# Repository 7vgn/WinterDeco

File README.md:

# Winter Decoration

Every year since 2023, I have created a winter-themed piece of decoration based on a custom-made PCB. The primary goal was to get some SMD soldering practice, but they also make nice presents. 

* [Evergreen Tree](2023/) (2023)
* [Simon the Snowman](2024/) (2024)
* [Old-fashioned Computer](2025/) (2025)
* [Spider Web](2026/) (2026)

All projects run on a CR2032 coin cell and feature the [PIC18F14Q41](https://www.microchip.com/en-us/product/pic18f14q41) microcontroller. The firmware was developed in [MPLAB X](https://www.microchip.com/en-us/tools-resources/develop/mplab-x-ide) using the [XC8](https://www.microchip.com/en-us/tools-resources/develop/mplab-xc-compilers/xc8) compiler. You need a PIC programmer such as PICkit, SNAP, or a suitable third-party clone to flash the firmware. 

The PCBs were designed with [KiCAD](https://www.kicad.org/). Ready-to-manufacture Gerber files for JLCPCB are included.

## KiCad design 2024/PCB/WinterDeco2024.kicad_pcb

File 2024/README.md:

# Winter Decoration 2024

The 2024 winter-themed decoration is Simon the Snowman. Simon has five touch-sensitive buttons. A long press of the lower right button turns him on of off. When turned on, a short press on each of the five buttons switches to a unique program. Simon also has a hidden secret game. Can you find it without looking at the code?

The touch sensors are implemented using the [PIC18F14Q41](https://www.microchip.com/en-us/product/pic18f14q41)'s capacitive voltage divider (CVD) feature. You can learn more about CVD in Microchip's Application Notes [1478](https://ww1.microchip.com/downloads/en/appnotes/01478A.pdf) and [2934](https://ww1.microchip.com/downloads/en/AppNotes/AN2934-Capacitive-Touch-Sensor-Design-Guidelines-00002934A.pdf). 

## Bill of Materials

| Ref | Qty | Part | Value | Links[^links]
| --- | ---:| --- | --- | --- |
| - | 1 | PCB | 2-layer, 1.6mm thickness, white soldermask, black silkscreen, ENIG[^enig] | [J](https://jlcpcb.com/)
| BT1 | 1 | Battery Clip | CR2032, SMD mount | [M](https://mouser.com/ProductDetail/?qs=sGAEpiMZZMvxqoKe%252BDjhrhkd9JgmX6KPIe2Fc6FHFcOAlHTLYwGDJA%3D%3D) [D](https://www.digikey.com/en/products/detail/te-connectivity-linx/BAT-HLD-003-SMT-TR/14301788?s=N4IgTCBcDaIEIEEAqBaAEgGQCIoAy4GYUBlAWVSQCUQBdAXyA) [R](https://www.reichelt.de/shop/produkt/knopfzellenclip_fuer_20_mm_smd-56574)
| C1 | 1 | Capacitor | SMD 1206, 100µF, X5R | [M](https://mouser.com/ProductDetail/?qs=pUKx8fyJudDzdyEEakAKPA%3D%3D) [D](https://www.digikey.com/en/products/detail/murata-electronics/GRM31CR60J107KEA8L/16286000?s=N4IgTCBcDaIOICUCyBmAjAYQQNgAwCk1cB2AaQFEBBADgBkQBdAXyA) [R](https://www.reichelt.de/shop/produkt/mlcc_1206_100_f_6_3_v_-10_x5r-409219)
| D* | 12 | LED | SMD 1206, yellow | [M](https://mouser.com/ProductDetail/?qs=sGAEpiMZZMv0DJfhVcWlK%252BdbpgZMtcHOeXAaxJ3bARo%3D) [D](https://www.digikey.com/en/products/detail/liteon/LTST-C150YKT/269217?s=N4IgTCBcDaIDIBUDKCC0BhAjAVgAwE0BpBEAXQF8g) [R](https://www.reichelt.de/shop/produkt/led_smd_1206_gelb_150_mcd_120_-361548)
| D* | 6 | LED | SMD 1206, red (mouth) | [M](https://mouser.com/ProductDetail/?qs=sGAEpiMZZMv0DJfhVcWlK%252BdbpgZMtcHOPtGkXd2H%2F2o%3D) [D](https://www.digikey.com/en/products/detail/liteon/LTST-C150KRKT/386761?s=N4IgTCBcDaIDIBUDKCC0BhAjAVgAwGkAlfBEAXQF8g) [R](https://www.reichelt.de/de/de/shop/produkt/led_smd_1206_rot_150_mcd_120_-361547)
| D* | 5 | LED | SMD 1206, green (buttons) | [M](https://mouser.com/ProductDetail/?qs=sGAEpiMZZMv0DJfhVcWlK%252BdbpgZMtcHOivY63VReAjk%3D) [D](https://www.digikey.com/en/products/detail/liteon/LTST-C150KGKT/365085?s=N4IgTCBcDaIDIBUDKCC0BhAjAVgAwGkBxfBEAXQF8g) [R](https://www.reichelt.de/de/de/shop/produkt/led_smd_1206_gruen_500_mcd_120_-361549)
| D* | 1 | LED | SMD 1206, orange (nose) | [M](https://mouser.com/ProductDetail/?qs=sGAEpiMZZMv0DJfhVcWlK%252BdbpgZMtcHO1szBFqLoZwU%3D) [D](https://www.digikey.com/en/products/detail/liteon/LTST-C150KFKT/386758?s=N4IgTCBcDaIDIBUDKCC0BhAjAVgAwGkAxfBEAXQF8g) [R](https://www.reichelt.de/de/de/shop/produkt/smd-led_superhell_orange_200_mcd_120_3_2_x_1_6_mm_1206_-231710)
| Q1[^polprot] | 1 | P-MOSFET | IRLML6402, SOT-23 | [M](https://mouser.com/ProductDetail/?qs=9%252BKlkBgLFf0HuZuONx2Ewg%3D%3D) [D](https://www.digikey.com/en/products/detail/infineon-technologies/IRLML6402TRPBF/811437) [R](https://www.reichelt.de/shop/produkt/mosfet_p-ch_-20v_-3_7a_0_065r_sot-23-108743)
| R1..4 | 4 | Resistor | SMD 1206, 68Ω | [M](https://mouser.com/ProductDetail/?qs=CteSnpDdeuDJTICysoGhNw%3D%3D) [D](https://www.digikey.com/en/products/detail/yageo/RC1206JR-0768RL/729330?s=N4IgTCBcDaIEoGECMYAMA2AUnAtKg7OgBxwAyIAugL5A) [R](https://www.reichelt.de/shop/produkt/smd-widerstand_1206_68_ohm_250_mw_5_-18364)
| R5 | 1 | Resistor | SMD 1206, 3.3kΩ | [M](https://mouser.com/ProductDetail/?qs=CteSnpDdeuDJAlQtfVL%252BIw%3D%3D) [D](https://www.digikey.com/en/products/detail/yageo/RC1206JR-073K3L/729267?s=N4IgTCBcDaIEoGECMYAMA2AUnAtKg7AMwDShAMiALoC%2BQA) [R](https://www.reichelt.de/shop/produkt/smd-widerstand_1206_3_3_kohm_250_mw_5_-18302)
| R6 | 1 | Resistor | SMD 1206, 4.7kΩ | [M](https://mouser.com/ProductDetail/?qs=CteSnpDdeuDgOu3Rsm1uRA%3D%3D) [D](https://www.digikey.com/en/products/detail/yageo/RC1206JR-074K7L/729295?s=N4IgTCBcDaIEoGECMYAMA2AUnAtKg7ACwDS%2BAMiALoC%2BQA) [R](https://www.reichelt.de/shop/produkt/smd-widerstand_1206_4_7_kohm_250_mw_5_-18330)
| U1 | 1 | Microcontroller | PIC18F14Q41-I/SO, SOIC-14 | [M](https://mouser.com/ProductDetail/?qs=W%2FMpXkg%252BdQ5jNCMT7LkJWg%3D%3D) [D](https://www.digikey.com/en/products/detail/microchip-technology/PIC18F14Q41-I-SO/13415037?s=N4IgTCBcDaIA4EsDGBGAHAMxQFgI7ZQFoEB6AZwHsQBdAXyA) [R](https://www.reichelt.de/shop/produkt/8-bit-picmicro_mikrocontroller_16_kb_64_mhz_so-20-311092)
| - | 1 | Piece of String | |
| - | 1 | Coin Cell | CR2032 |

[^links]: Links are just examples. Other sellers are available and similar parts can be substituted.  
[^enig]: ENIG is not required, but at JLCPCB the combination of white soldermask and lead-free HASL comes with a surcharge which makes ENIG the cheaper option.  
[^polprot]: Q1 protects against reverse polarity and is optional. If left out, the solder jumper JP1 must be bridged instead. 

Required tools and materials: soldering iron, lead-free solder, tweezers, flux, isopropyl alcohol for cleaning, PIC programmer

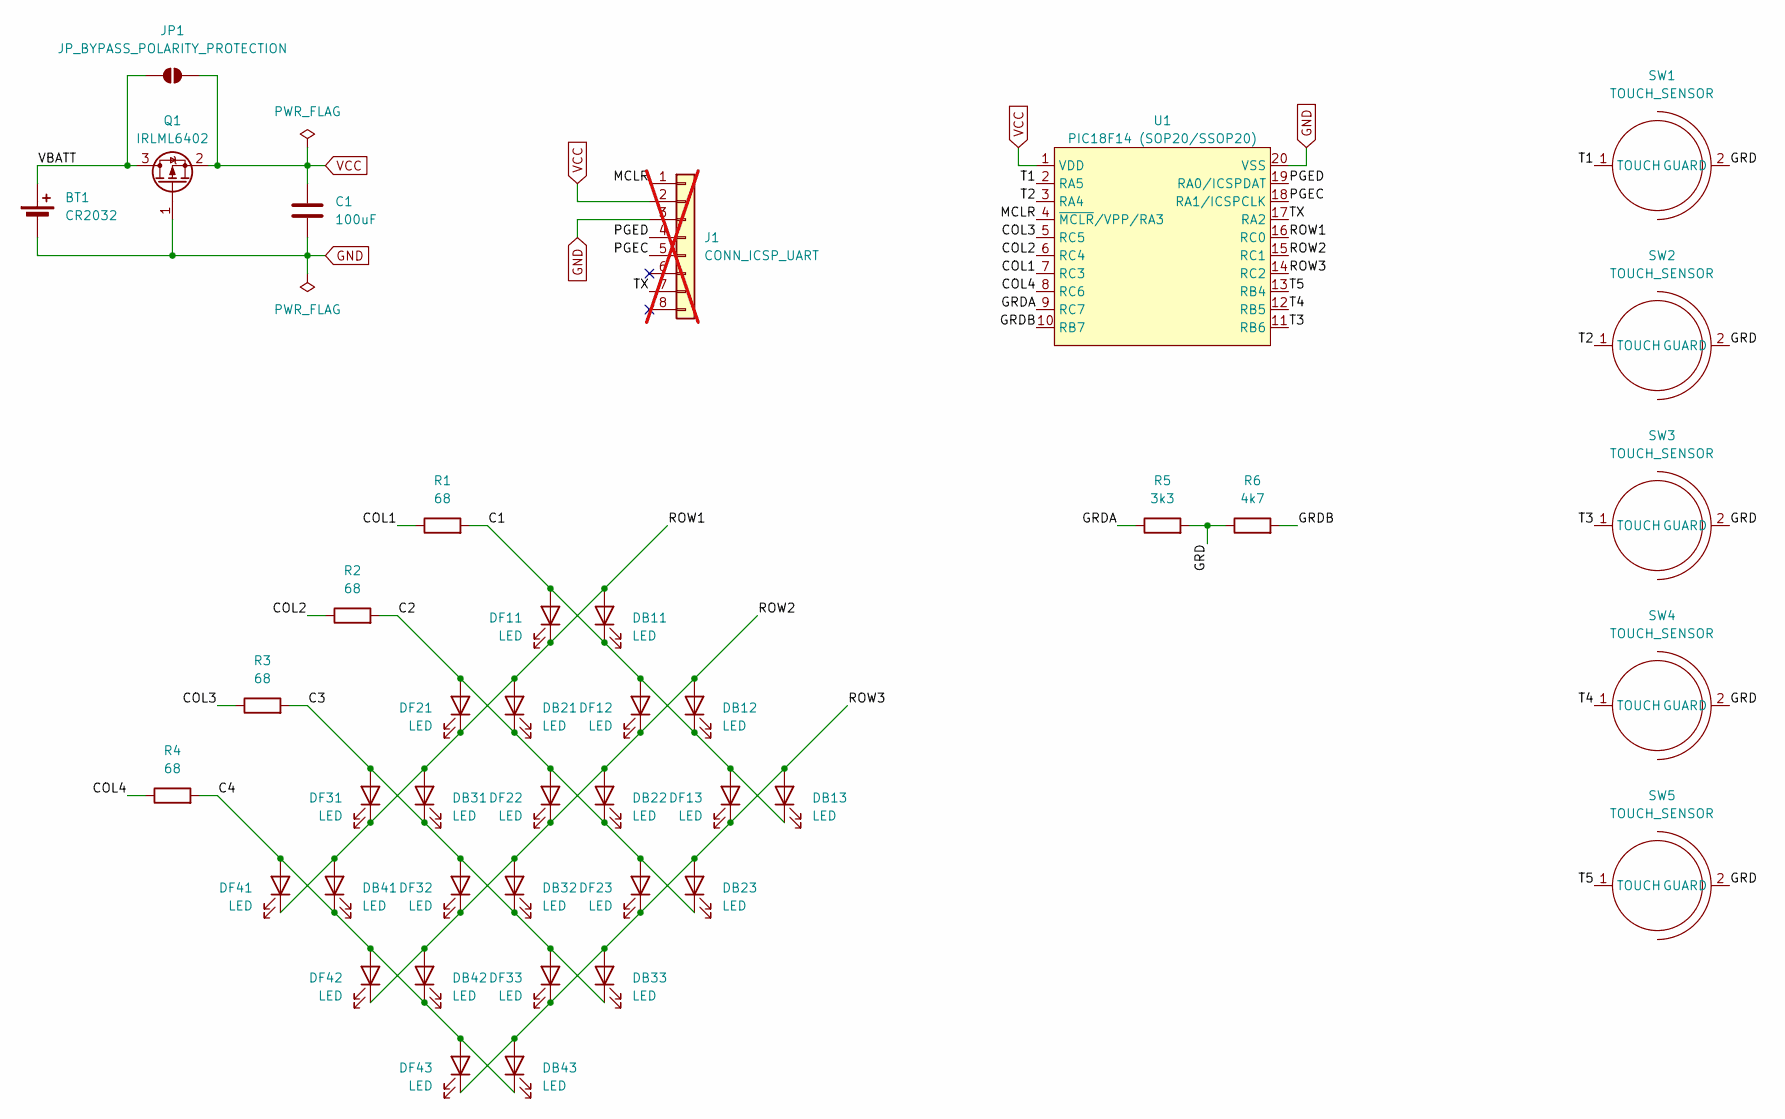
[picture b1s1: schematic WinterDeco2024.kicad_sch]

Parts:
BT1: CR2032; BatteryHolder_Keystone_3002_1x2032
C1: 100uF; C_1206_3216Metric_Pad1.33x1.80mm_HandSolder
DB11, DB12, DB13, DB21, DB22, DB23, DB31, DB32, DB33, DB41, DB42, DB43: LED; LED_1206_3216Metric_Pad1.42x1.75mm_Arrow_HandSolder
DF11, DF12, DF13, DF21, DF22, DF23, DF31, DF32, DF33, DF41, DF42, DF43: LED; LED_1206_3216Metric_Pad1.42x1.75mm_Arrow_HandSolder
J1: CONN_ICSP_UART; PinHeader_1x08_P2.54mm_Vertical; not fitted
JP1: JP_BYPASS_POLARITY_PROTECTION; SolderJumper-2_P1.3mm_Open_RoundedPad1.0x1.5mm
Q1: IRLML6402; SOT-23
R1, R2, R3, R4: 68; R_1206_3216Metric_Pad1.30x1.75mm_HandSolder
R5: 3k3; R_1206_3216Metric_Pad1.30x1.75mm_HandSolder
R6: 4k7; R_1206_3216Metric_Pad1.30x1.75mm_HandSolder
SW1, SW2, SW3, SW4, SW5: TOUCH_SENSOR; Touch Sensor Thin
U1: PIC18F14 (SOP20/SSOP20); SO-20_12.8x7.5mm_P1.27mm

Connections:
/C1: DB11.1 (K), DB12.1 (K), DB13.1 (K), DF11.2 (A), DF12.2 (A), DF13.2 (A), R1.2
/C2: DB21.1 (K), DB22.1 (K), DB23.1 (K), DF21.2 (A), DF22.2 (A), DF23.2 (A), R2.2
/C3: DB31.1 (K), DB32.1 (K), DB33.1 (K), DF31.2 (A), DF32.2 (A), DF33.2 (A), R3.2
/C4: DB41.1 (K), DB42.1 (K), DB43.1 (K), DF41.2 (A), DF42.2 (A), DF43.2 (A), R4.2
/COL1: R1.1, U1.7 (RC3)
/COL2: R2.1, U1.6 (RC4)
/COL3: R3.1, U1.5 (RC5)
/COL4: R4.1, U1.8 (RC6)
/GRD: R5.2, R6.1, SW1.2 (GUARD), SW2.2 (GUARD), SW3.2 (GUARD), SW4.2 (GUARD), SW5.2 (GUARD)
/GRDA: R5.1, U1.9 (RC7)
/GRDB: R6.2, U1.10 (RB7)
/MCLR: J1.1, U1.4 (~MCLR/VPP/RA3)
/PGEC: J1.5, U1.18 (RA1/ICSPCLK)
/PGED: J1.4, U1.19 (RA0/ICSPDAT)
/ROW1: DB11.2 (A), DB21.2 (A), DB31.2 (A), DB41.2 (A), DF11.1 (K), DF21.1 (K), DF31.1 (K), DF41.1 (K), U1.16 (RC0)
/ROW2: DB12.2 (A), DB22.2 (A), DB32.2 (A), DB42.2 (A), DF12.1 (K), DF22.1 (K), DF32.1 (K), DF42.1 (K), U1.15 (RC1)
/ROW3: DB13.2 (A), DB23.2 (A), DB33.2 (A), DB43.2 (A), DF13.1 (K), DF23.1 (K), DF33.1 (K), DF43.1 (K), U1.14 (RC2)
/T1: SW1.1 (TOUCH), U1.2 (RA5)
/T2: SW2.1 (TOUCH), U1.3 (RA4)
/T3: SW3.1 (TOUCH), U1.11 (RB6)
/T4: SW4.1 (TOUCH), U1.12 (RB5)
/T5: SW5.1 (TOUCH), U1.13 (RB4)
/TX: J1.7, U1.17 (RA2)
/VBATT: BT1.1 (+), JP1.1 (A), Q1.3 (D)
GND: BT1.2 (-), C1.2, J1.3, Q1.1 (G), U1.20 (VSS)
VCC: C1.1, J1.2, JP1.2 (B), Q1.2 (S), U1.1 (VDD)

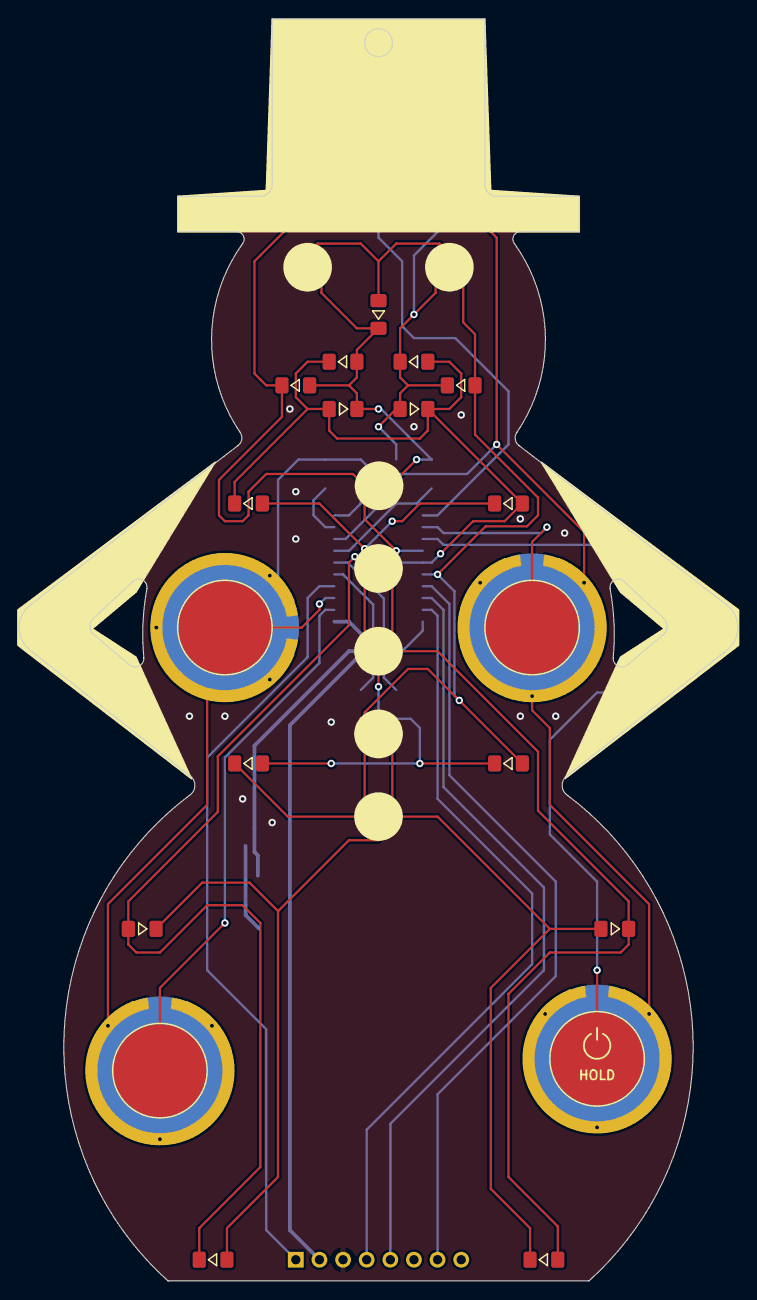
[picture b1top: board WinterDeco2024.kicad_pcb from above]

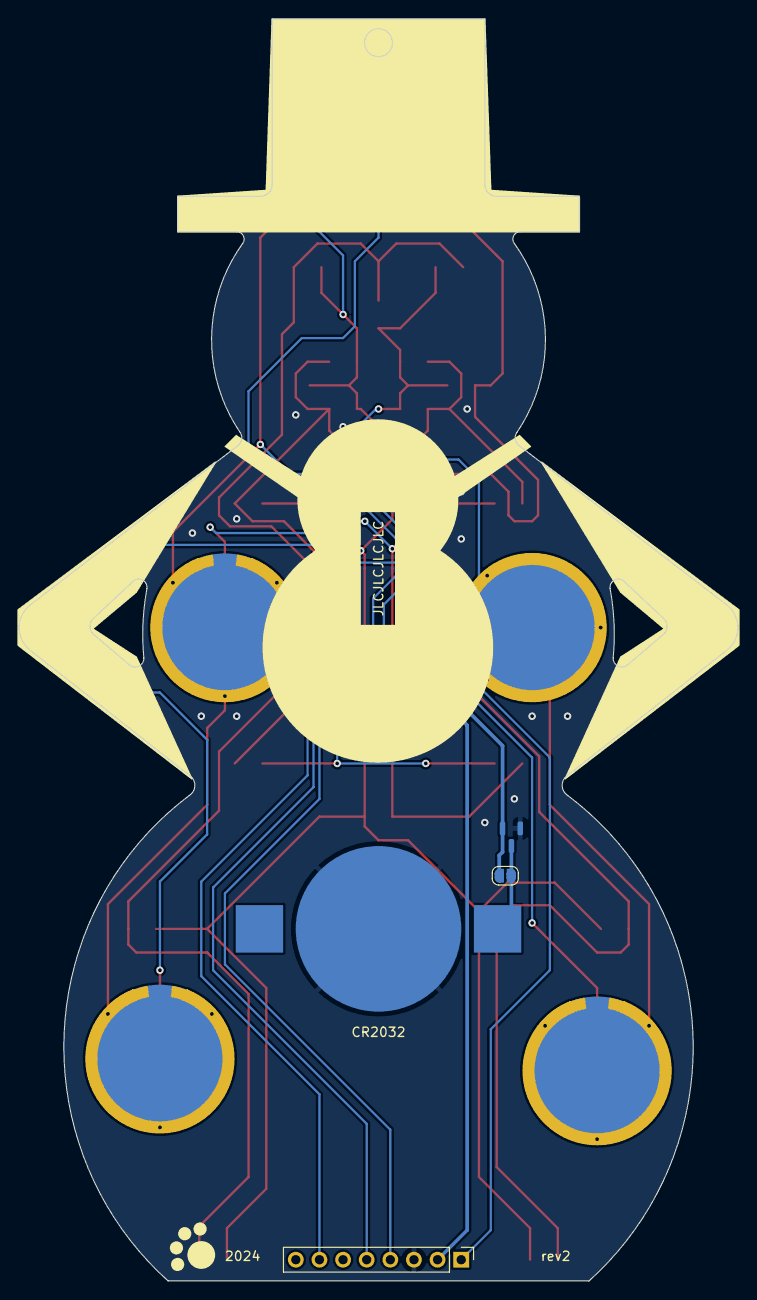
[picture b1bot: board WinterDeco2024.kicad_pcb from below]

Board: 2 copper layers, 77.3 x 135.6 mm, 41 parts (12 on the bottom side), 26 nets.

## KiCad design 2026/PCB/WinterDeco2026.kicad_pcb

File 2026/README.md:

> [!NOTE]
> This is a work in progress.

# Winter Decoration 2026

The 2025 winter-themed decoration is a spider web. This piece has no buttons or touch sensors at all, instead it uses an accelerometer. 
As always, there is a hidden game. Can you find it without looking at the code?

## Bill of Materials

| Ref | Qty | Part | Value | Links[^links]
| --- | ---:| --- | --- | --- |
| - | 1 | PCB | 2-layer, 1.6mm thickness, purple soldermask, lead-free HASL | [J](https://jlcpcb.com/)
| BT1 | 1 | Battery Clip | CR2032, SMD mount | [M](https://mouser.com/ProductDetail/?qs=sGAEpiMZZMvxqoKe%252BDjhrhkd9JgmX6KPIe2Fc6FHFcOAlHTLYwGDJA%3D%3D) [D](https://www.digikey.com/en/products/detail/te-connectivity-linx/BAT-HLD-003-SMT-TR/14301788?s=N4IgTCBcDaIEIEEAqBaAEgGQCIoAy4GYUBlAWVSQCUQBdAXyA) [R](https://www.reichelt.de/shop/produkt/knopfzellenclip_fuer_20_mm_smd-56574)
| C1 | 1 | Capacitor | SMD 1206, 100µF, X5R | [M](https://mouser.com/ProductDetail/?qs=pUKx8fyJudDzdyEEakAKPA%3D%3D) [D](https://www.digikey.com/en/products/detail/murata-electronics/GRM31CR60J107KEA8L/16286000?s=N4IgTCBcDaIOICUCyBmAjAYQQNgAwCk1cB2AaQFEBBADgBkQBdAXyA) [R](https://www.reichelt.de/shop/produkt/mlcc_1206_100_f_6_3_v_-10_x5r-409219)
| C2..3 | 2 | Capacitor | SMD 1206, 100nF, X7R | [M](https://mouser.com/ProductDetail/?qs=Jm2GQyTW%2Fbgjukwx9JJFzw%3D%3D) [D](https://www.digikey.com/en/products/detail/kyocera-avx/KGM31DR72A104KU/563639?s=N4IgTCBcDaIIxgAwDY4GE6ICwGkCCAKmHiALoC%2BQA) [R](https://www.reichelt.de/shop/produkt/mlcc_1206_100_nf_100_v_-10_x7r-409241)
| C4 | 1 | Capacitor | SMD 1206, 1µF, tantalum | [M](https://mouser.com/ProductDetail/?qs=rZB7yXOqaoskTND3m0TpXQ%3D%3D) [D](https://www.digikey.com/en/products/detail/kemet/T491A105K016AT/818539) [R](https://www.reichelt.de/shop/produkt/smd-tantal_1_f_16v_125_c-393782)
| D1 | 1 | Photodiode | Infrared (850nm), 3mm | [M](https://mouser.com/ProductDetail/?qs=mAH9sUMRCttalcwxTBHy7g%3D%3D) [D](https://www.digikey.com/en/products/detail/inolux/INL-3ANPD80/10384782?s=N4IgTCBcDaIJIDkAyBaAzAQQQBQCIA4AGEAXQF8g) [A](https://aliexpress.com/item/1005007219440978.html)
| D* | 31 | LED | SMD 1206, yellow | [M](https://mouser.com/ProductDetail/?qs=sGAEpiMZZMv0DJfhVcWlK%252BdbpgZMtcHOeXAaxJ3bARo%3D) [D](https://www.digikey.com/en/products/detail/liteon/LTST-C150YKT/269217?s=N4IgTCBcDaIDIBUDKCC0BhAjAVgAwE0BpBEAXQF8g) [R](https://www.reichelt.de/shop/produkt/led_smd_1206_gelb_150_mcd_120_-361548)
| D* | 1 | LED | SMD 1206, red (back side) | [M](https://mouser.com/ProductDetail/?qs=sGAEpiMZZMv0DJfhVcWlK%252BdbpgZMtcHOPtGkXd2H%2F2o%3D) [D](https://www.digikey.com/en/products/detail/liteon/LTST-C150KRKT/386761?s=N4IgTCBcDaIDIBUDKCC0BhAjAVgAwGkAlfBEAXQF8g) [R](https://www.reichelt.de/de/de/shop/produkt/led_smd_1206_rot_150_mcd_120_-361547)
| Q1[^polprot] | 1 | P-MOSFET | IRLML6402, SOT-23 | [M](https://mouser.com/ProductDetail/?qs=9%252BKlkBgLFf0HuZuONx2Ewg%3D%3D) [D](https://www.digikey.com/en/products/detail/infineon-technologies/IRLML6402TRPBF/811437) [R](https://www.reichelt.de/shop/produkt/mosfet_p-ch_-20v_-3_7a_0_065r_sot-23-108743)
| R1..4 | 4 | Resistor | SMD 1206, 68Ω | [M](https://mouser.com/ProductDetail/?qs=CteSnpDdeuDJTICysoGhNw%3D%3D) [D](https://www.digikey.com/en/products/detail/yageo/RC1206JR-0768RL/729330?s=N4IgTCBcDaIEoGECMYAMA2AUnAtKg7OgBxwAyIAugL5A) [R](https://www.reichelt.de/shop/produkt/smd-widerstand_1206_68_ohm_250_mw_5_-18364)
| R5..6 | 2 | Resistor | SMD 1206, 4.7kΩ | [M](https://mouser.com/ProductDetail/?qs=CteSnpDdeuDgOu3Rsm1uRA%3D%3D) [D](https://www.digikey.com/en/products/detail/yageo/RC1206JR-074K7L/729295?s=N4IgTCBcDaIEoGECMYAMA2AUnAtKg7ACwDS%2BAMiALoC%2BQA) [R](https://www.reichelt.de/shop/produkt/smd-widerstand_1206_4_7_kohm_250_mw_5_-18330)
| U1 | 1 | Microcontroller | PIC18F14Q41-I/REB, VQFN-20 | [M](https://mouser.com/ProductDetail/?qs=W%2FMpXkg%252BdQ7pNqp6ZZCcjA%3D%3D) [D](https://www.digikey.com/en/products/detail/microchip-technology/PIC18F14Q41-I-REB/13622176?s=N4IgTCBcDaIAoEkDCBGAHAMRQFgIrZQFoEB6AJQFEAhEAXQF8g) [R](https://www.reichelt.de/shop/produkt/8-bit-picmicro_mikrocontroller_16_kb_64_mhz_vqfn-20-311094)
| U2 | 1 | Accelerometer | ADXL345, LGA-14 | [M](https://mouser.com/ProductDetail/?qs=WIvQP4zGanhoa7YOkGtvEg%3D%3D) [D](https://www.digikey.com/en/products/detail/analog-devices-inc/ADXL345BCCZ/2034829) [A](https://aliexpress.com/item/1005008097141961.html)
| - | 1 | Piece of String | |
| - | 1 | Coin Cell | CR2032 |

[^links]: Links are just examples. Other sellers are available and similar parts can be substituted.  
[^polprot]: Q1 protects against reverse polarity and is optional. If left out, the solder jumper JP1 must be bridged instead. 

Required tools and materials: soldering iron, lead-free solder, hot air station, solder paste, tweezers, flux, isopropyl alcohol for cleaning, PIC programmer

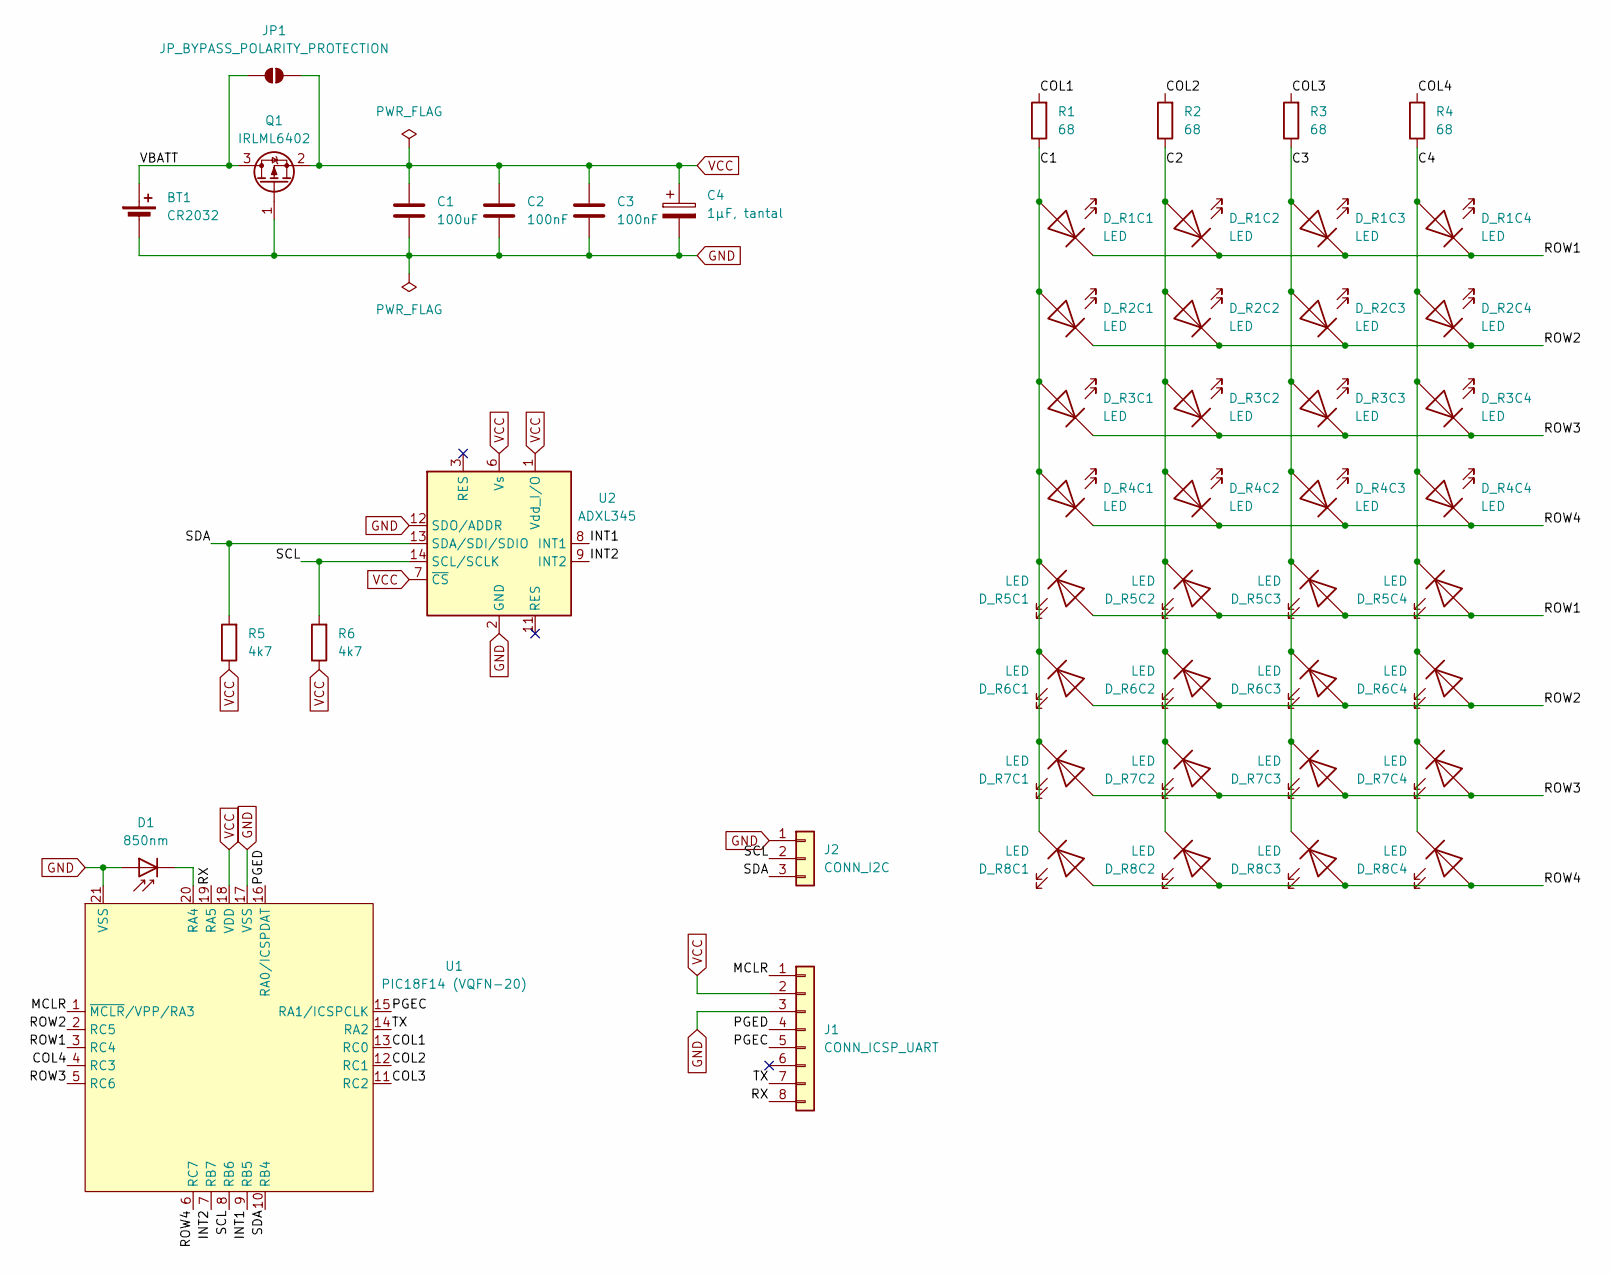
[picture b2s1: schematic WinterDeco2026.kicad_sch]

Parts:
BT1: CR2032; BatteryHolder_Keystone_3002_1x2032
C1: 100uF; C_1206_3216Metric_Pad1.33x1.80mm_HandSolder
C2, C3: 100nF; C_1206_3216Metric_Pad1.33x1.80mm_HandSolder
C4: 1µF, tantal; CP_EIA-3216-18_Kemet-A_HandSolder
D1: 850nm; LED_D3.0mm
D_R1C1, D_R1C2, D_R1C3, D_R1C4, D_R2C1, D_R2C2, D_R2C3, D_R2C4, D_R3C1, D_R3C2, D_R3C3, D_R3C4, D_R4C1, D_R4C2, D_R4C3, D_R4C4, D_R5C1, D_R5C2, D_R5C3, D_R5C4, D_R6C1, D_R6C2, D_R6C3, D_R6C4, D_R7C1, D_R7C2, D_R7C3, D_R7C4, D_R8C1, D_R8C2, D_R8C3, D_R8C4: LED; LED_1206_3216Metric_Pad1.42x1.75mm_Arrow_HandSolder
J1: CONN_ICSP_UART; PinHeader_1x08_P2.54mm_Vertical
J2: CONN_I2C; JST_SH_BM03B-SRSS-TB_1x03-1MP_P1.00mm_Vertical
JP1: JP_BYPASS_POLARITY_PROTECTION; SolderJumper-2_P1.3mm_Open_RoundedPad1.0x1.5mm
Q1: IRLML6402; SOT-23
R1, R2, R3, R4: 68; R_1206_3216Metric_Pad1.30x1.75mm_HandSolder
R5, R6: 4k7; R_1206_3216Metric_Pad1.30x1.75mm_HandSolder
U1: PIC18F14 (VQFN-20); VQFN-20-1EP_3x3mm_P0.4mm_EP1.7x1.7mm
U2: ADXL345; LGA-14_3x5mm_P0.8mm_LayoutBorder1x6y

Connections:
/C1: D_R1C1.2 (A), D_R2C1.2 (A), D_R3C1.2 (A), D_R4C1.2 (A), D_R5C1.1 (K), D_R6C1.1 (K), D_R7C1.1 (K), D_R8C1.1 (K), R1.1
/C2: D_R1C2.2 (A), D_R2C2.2 (A), D_R3C2.2 (A), D_R4C2.2 (A), D_R5C2.1 (K), D_R6C2.1 (K), D_R7C2.1 (K), D_R8C2.1 (K), R2.1
/C3: D_R1C3.2 (A), D_R2C3.2 (A), D_R3C3.2 (A), D_R4C3.2 (A), D_R5C3.1 (K), D_R6C3.1 (K), D_R7C3.1 (K), D_R8C3.1 (K), R3.1
/C4: D_R1C4.2 (A), D_R2C4.2 (A), D_R3C4.2 (A), D_R4C4.2 (A), D_R5C4.1 (K), D_R6C4.1 (K), D_R7C4.1 (K), D_R8C4.1 (K), R4.1
/COL1: R1.2, U1.13 (RC0)
/COL2: R2.2, U1.12 (RC1)
/COL3: R3.2, U1.11 (RC2)
/COL4: R4.2, U1.4 (RC3)
/INT1: U1.9 (RB5), U2.8 (INT1)
/INT2: U1.7 (RB7), U2.9 (INT2)
/MCLR: J1.1, U1.1 (~MCLR/VPP/RA3)
/PGEC: J1.5, U1.15 (RA1/ICSPCLK)
/PGED: J1.4, U1.16 (RA0/ICSPDAT)
/ROW1: D_R1C1.1 (K), D_R1C2.1 (K), D_R1C3.1 (K), D_R1C4.1 (K), D_R5C1.2 (A), D_R5C2.2 (A), D_R5C3.2 (A), D_R5C4.2 (A), U1.3 (RC4)
/ROW2: D_R2C1.1 (K), D_R2C2.1 (K), D_R2C3.1 (K), D_R2C4.1 (K), D_R6C1.2 (A), D_R6C2.2 (A), D_R6C3.2 (A), D_R6C4.2 (A), U1.2 (RC5)
/ROW3: D_R3C1.1 (K), D_R3C2.1 (K), D_R3C3.1 (K), D_R3C4.1 (K), D_R7C1.2 (A), D_R7C2.2 (A), D_R7C3.2 (A), D_R7C4.2 (A), U1.5 (RC6)
/ROW4: D_R4C1.1 (K), D_R4C2.1 (K), D_R4C3.1 (K), D_R4C4.1 (K), D_R8C1.2 (A), D_R8C2.2 (A), D_R8C3.2 (A), D_R8C4.2 (A), U1.6 (RC7)
/RX: J1.8, U1.19 (RA5)
/SCL: J2.2, R6.2, U1.8 (RB6), U2.14 (SCL/SCLK)
/SDA: J2.3, R5.2, U1.10 (RB4), U2.13 (SDA/SDI/SDIO)
/TX: J1.7, U1.14 (RA2)
/VBATT: BT1.1 (+), JP1.1 (A), Q1.3 (D)
GND: BT1.2 (-), C1.2, C2.2, C3.2, C4.2, D1.2 (A), J1.3, J2.1, Q1.1 (G), U1.17 (VSS), U1.21 (VSS), U2.2 (GND), U2.4 (GND), U2.5 (GND), U2.12 (SDO/ADDR)
unnamed: D1.1 (K), U1.20 (RA4)
VCC: C1.1, C2.1, C3.1, C4.1, J1.2, JP1.2 (B), Q1.2 (S), R5.1, R6.1, U1.18 (VDD), U2.1 (Vdd_I/O), U2.6 (Vs), U2.7 (~CS)

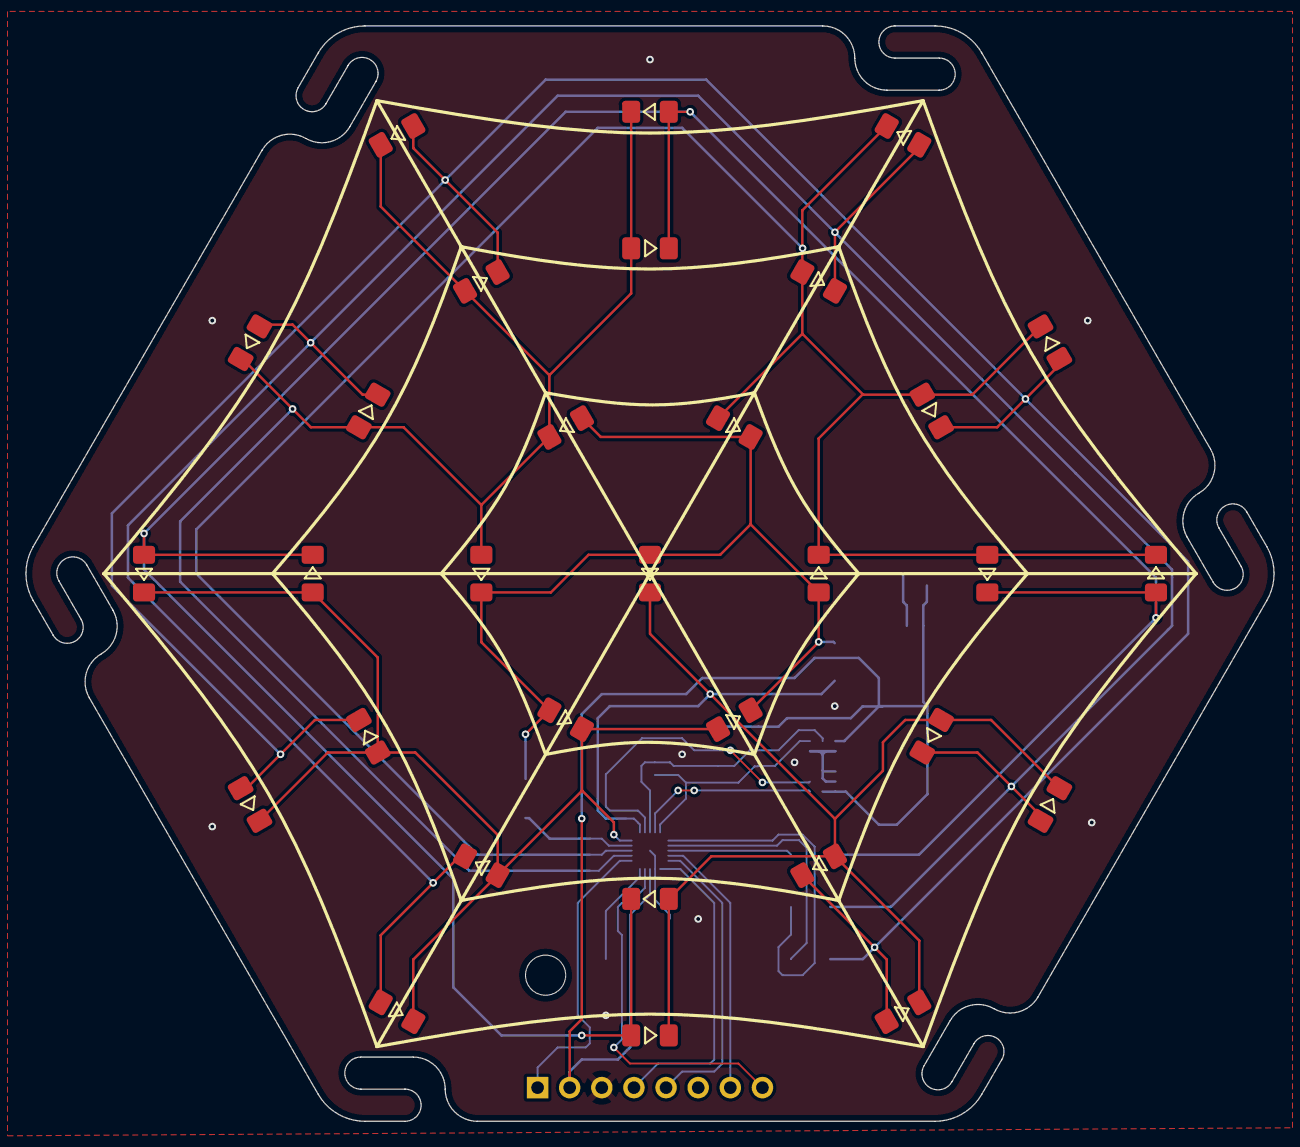
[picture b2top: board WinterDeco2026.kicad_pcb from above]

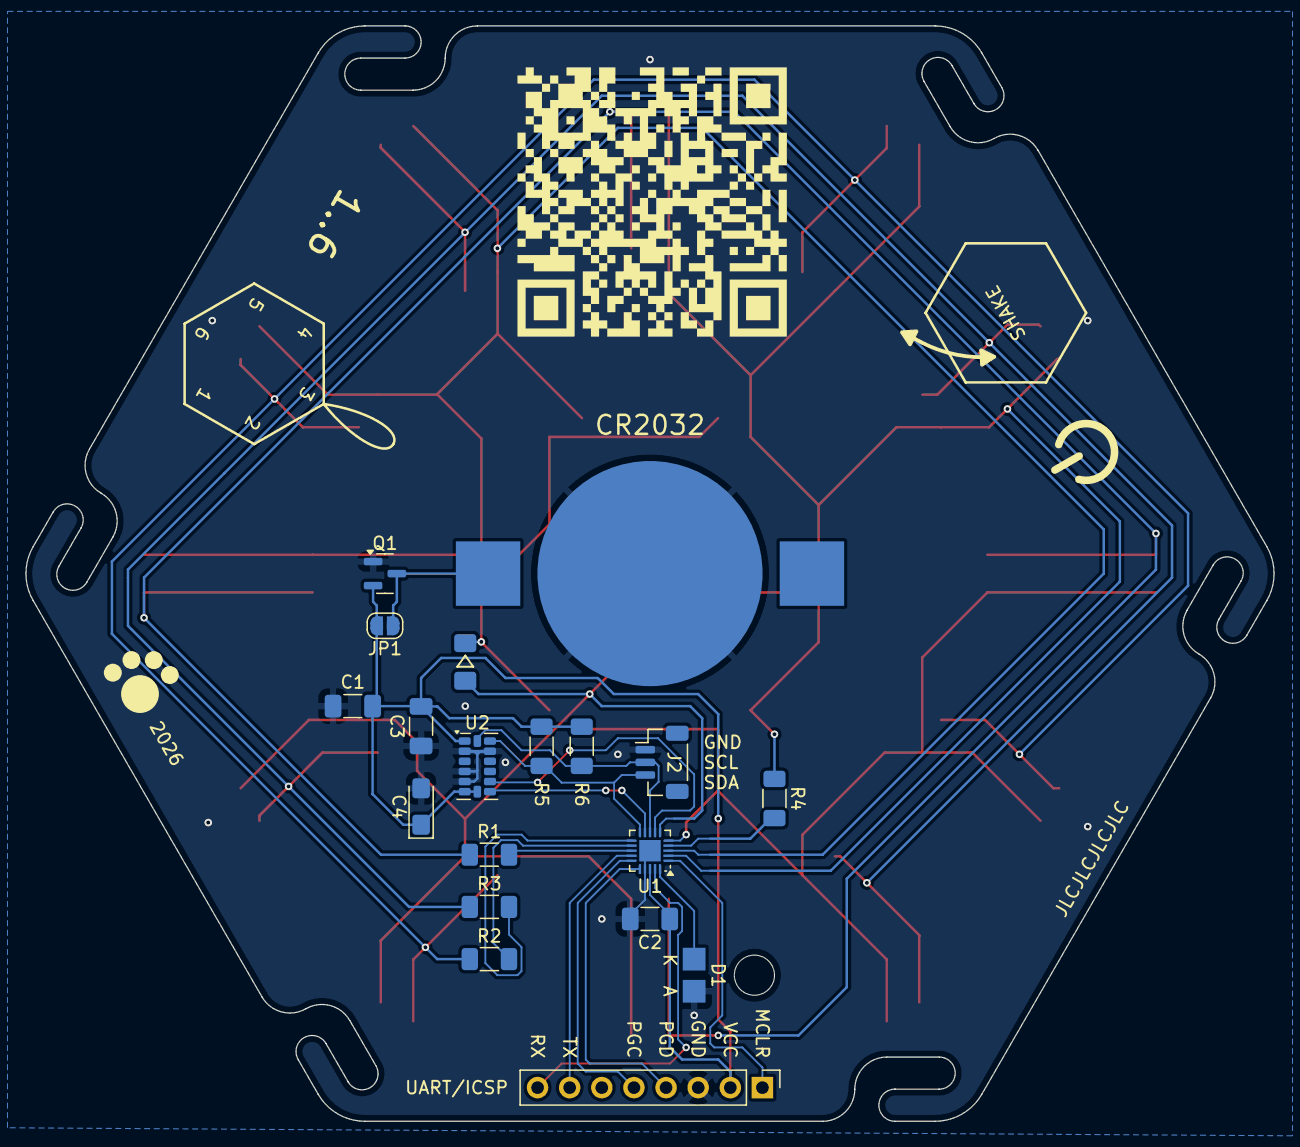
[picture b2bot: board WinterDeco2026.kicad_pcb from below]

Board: 2 copper layers, 98.7 x 86.6 mm, 50 parts (19 on the bottom side), 25 nets.

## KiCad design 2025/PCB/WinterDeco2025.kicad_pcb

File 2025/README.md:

# Winter Decoration 2025

The 2025 winter-themed decoration mimics the aesthetics of an old-fashioned 90s-style computer. True to form, it uses clicky buttons instead of touch sensors. The screen resolution of 8x8 pixels is also reminiscent of bygone days. Just like last year, there is a hidden game. Can you find it without looking at the code?

## Bill of Materials

| Ref | Qty | Part | Value | Links[^links]
| --- | ---:| --- |
| - | 1 | PCB | 2-layer, 1.6mm thickness, blue soldermask, lead-free HASL | [J](https://jlcpcb.com/)
| BT1 | 1 | Battery Clip | CR2032, SMD mount | [M](https://mouser.com/ProductDetail/?qs=sGAEpiMZZMvxqoKe%252BDjhrhkd9JgmX6KPIe2Fc6FHFcOAlHTLYwGDJA%3D%3D) [D](https://www.digikey.com/en/products/detail/te-connectivity-linx/BAT-HLD-003-SMT-TR/14301788?s=N4IgTCBcDaIEIEEAqBaAEgGQCIoAy4GYUBlAWVSQCUQBdAXyA) [R](https://www.reichelt.de/shop/produkt/knopfzellenclip_fuer_20_mm_smd-56574)
| C1 | 1 | Capacitor | SMD 1206, 100µF, X5R | [M](https://mouser.com/ProductDetail/?qs=pUKx8fyJudDzdyEEakAKPA%3D%3D) [D](https://www.digikey.com/en/products/detail/murata-electronics/GRM31CR60J107KEA8L/16286000?s=N4IgTCBcDaIOICUCyBmAjAYQQNgAwCk1cB2AaQFEBBADgBkQBdAXyA) [R](https://www.reichelt.de/shop/produkt/mlcc_1206_100_f_6_3_v_-10_x5r-409219)
| C2..3 | 2 | Capacitor | SMD 1206, 100nF, X7R | [M](https://mouser.com/ProductDetail/?qs=Jm2GQyTW%2Fbgjukwx9JJFzw%3D%3D) [D](https://www.digikey.com/en/products/detail/kyocera-avx/KGM31DR72A104KU/563639?s=N4IgTCBcDaIIxgAwDY4GE6ICwGkCCAKmHiALoC%2BQA) [R](https://www.reichelt.de/shop/produkt/mlcc_1206_100_nf_100_v_-10_x7r-409241)
| D* | 64 | LED | SMD 1206, yellow | [M](https://mouser.com/ProductDetail/?qs=sGAEpiMZZMv0DJfhVcWlK%252BdbpgZMtcHOeXAaxJ3bARo%3D) [D](https://www.digikey.com/en/products/detail/liteon/LTST-C150YKT/269217?s=N4IgTCBcDaIDIBUDKCC0BhAjAVgAwE0BpBEAXQF8g) [R](https://www.reichelt.de/shop/produkt/led_smd_1206_gelb_150_mcd_120_-361548)
| Q1[^polprot] | 1 | P-MOSFET | IRLML6402, SOT-23 | [M](https://mouser.com/ProductDetail/?qs=9%252BKlkBgLFf0HuZuONx2Ewg%3D%3D) [D](https://www.digikey.com/en/products/detail/infineon-technologies/IRLML6402TRPBF/811437) [R](https://www.reichelt.de/shop/produkt/mosfet_p-ch_-20v_-3_7a_0_065r_sot-23-108743)
| R1..4 | 4 | Resistor | SMD 1206, 68Ω | [M](https://mouser.com/ProductDetail/?qs=CteSnpDdeuDJTICysoGhNw%3D%3D) [D](https://www.digikey.com/en/products/detail/yageo/RC1206JR-0768RL/729330?s=N4IgTCBcDaIEoGECMYAMA2AUnAtKg7OgBxwAyIAugL5A) [R](https://www.reichelt.de/shop/produkt/smd-widerstand_1206_68_ohm_250_mw_5_-18364)
| SW1..3 | 3 | Push Buttons | B3FS-1000P | [M](https://mouser.com/ProductDetail/?qs=ImaqFqjHA4k6odVF2%2FXWpQ%3D%3D) [D](https://www.digikey.com/en/products/detail/omron-electronics-inc-emc-div/B3FS-1000P/277812?s=N4IgTCBcDaIEYGYBmBnAtARgAw4A4gF0BfIA) [R](https://www.reichelt.de/shop/produkt/taster_smd_1_schliesser_no_-243056)
| U1 | 1 | Microcontroller | PIC18F14Q41-I/SO, SOIC-14 | [M](https://mouser.com/ProductDetail/?qs=W%2FMpXkg%252BdQ5jNCMT7LkJWg%3D%3D) [D](https://www.digikey.com/en/products/detail/microchip-technology/PIC18F14Q41-I-SO/13415037?s=N4IgTCBcDaIA4EsDGBGAHAMxQFgI7ZQFoEB6AZwHsQBdAXyA) [R](https://www.reichelt.de/shop/produkt/8-bit-picmicro_mikrocontroller_16_kb_64_mhz_so-20-311092)
| U2 | 1 | Demultiplexer | 74HC154, SOIC-24 | [M](https://mouser.com/ProductDetail/?qs=YxwvVplHM%2FnR3vJab0%252BPQw%3D%3D) [D](https://www.digikey.com/en/products/detail/texas-instruments/CD74HC154M96/1506686) [R](https://www.reichelt.de/de/de/shop/produkt/decoder_4_to_16_2_6_v_so-24-18644)
| - | 1 | Piece of String | |
| - | 1 | Coin Cell | CR2032 |

[^links]: Links are just examples. Other sellers are available and similar parts can be substituted.  
[^polprot]: Q1 protects against reverse polarity and is optional. If left out, the solder jumper JP1 must be bridged instead. 

Required tools and materials: soldering iron, lead-free solder, tweezers, flux, isopropyl alcohol for cleaning, PIC programmer

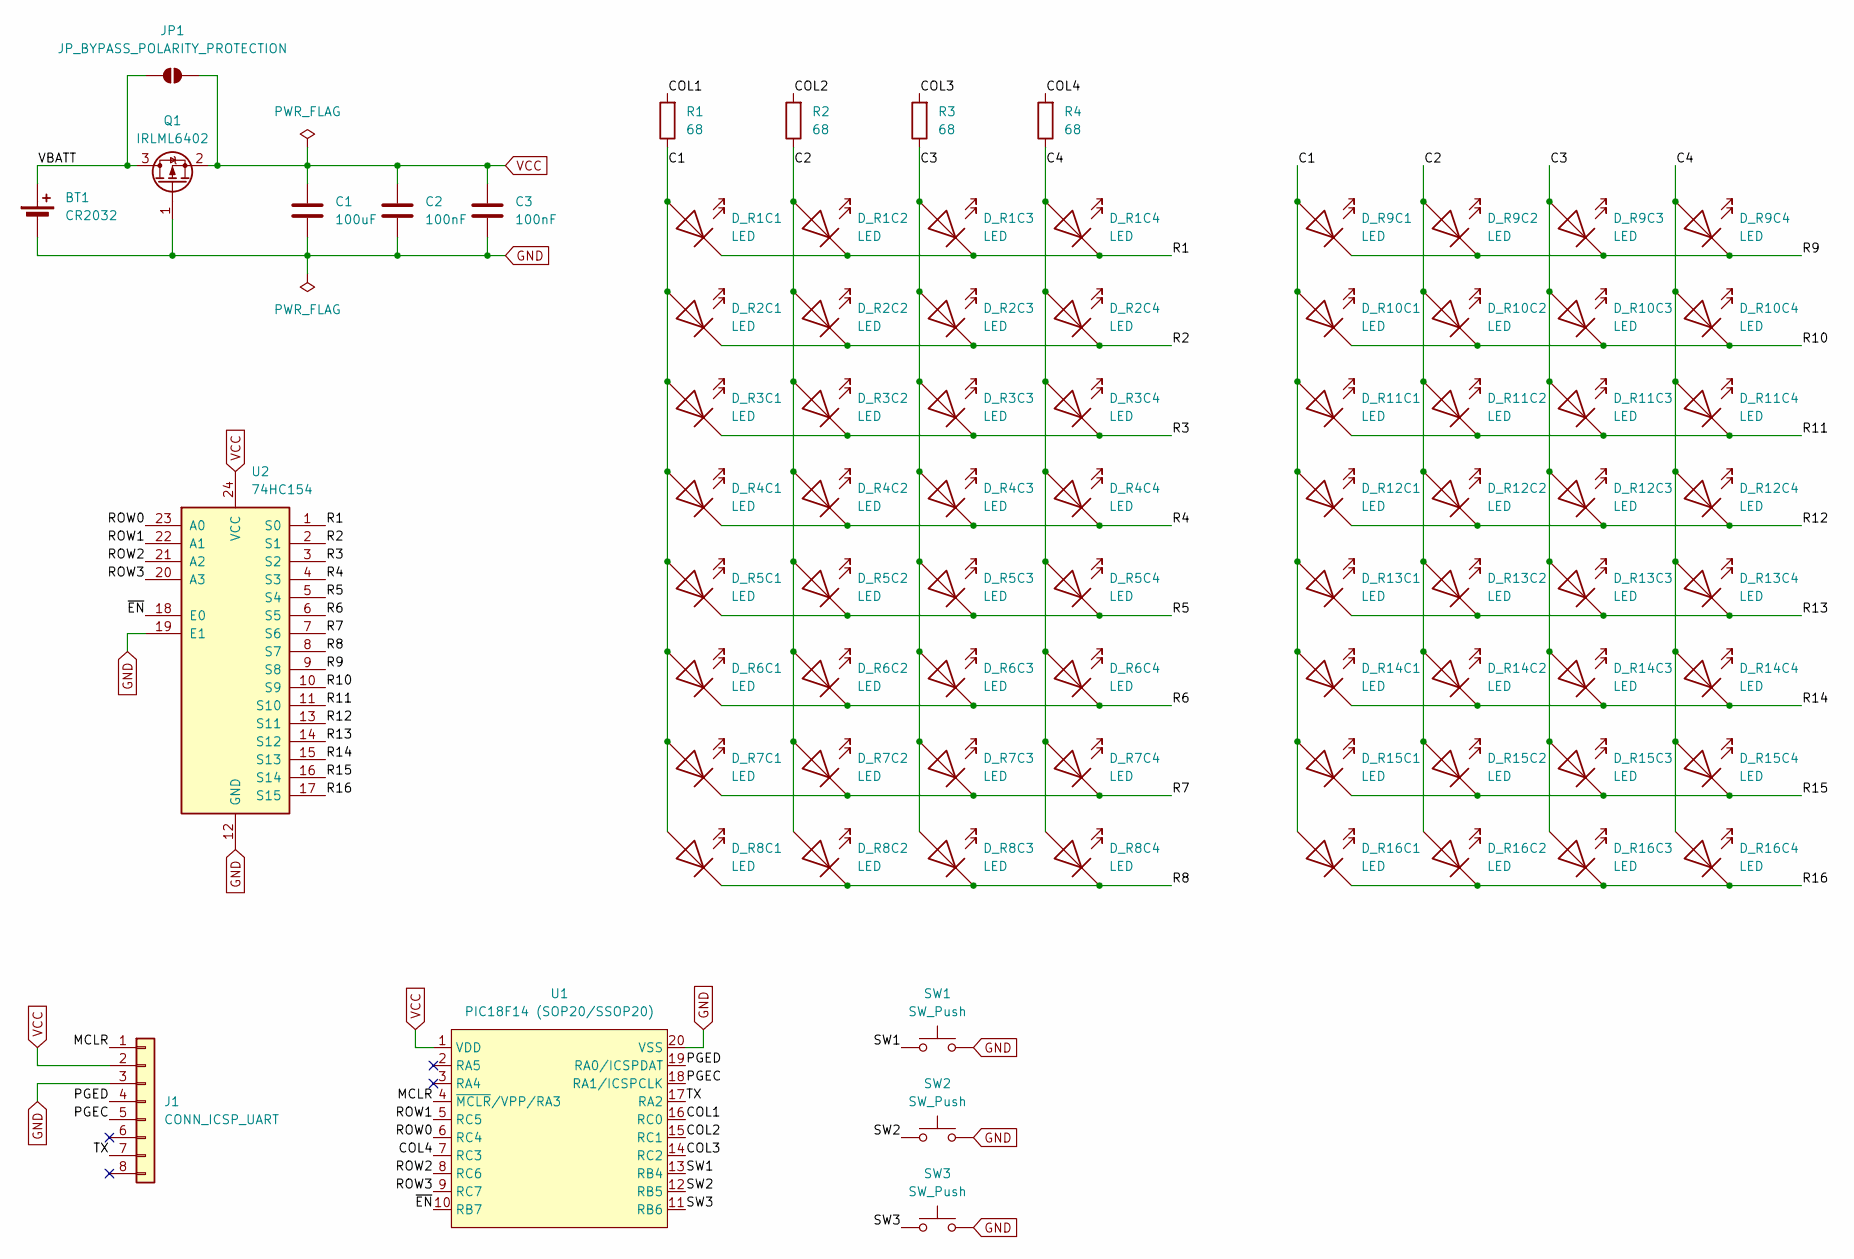
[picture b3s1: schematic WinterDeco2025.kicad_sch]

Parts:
BT1: CR2032; BatteryHolder_Keystone_3002_1x2032
C1: 100uF; C_1206_3216Metric_Pad1.33x1.80mm_HandSolder
C2, C3: 100nF; C_1206_3216Metric_Pad1.33x1.80mm_HandSolder
D_R1C1, D_R1C2, D_R1C3, D_R1C4, D_R2C1, D_R2C2, D_R2C3, D_R2C4, D_R3C1, D_R3C2, D_R3C3, D_R3C4, D_R4C1, D_R4C2, D_R4C3, D_R4C4, D_R5C1, D_R5C2, D_R5C3, D_R5C4, D_R6C1, D_R6C2, D_R6C3, D_R6C4, D_R7C1, D_R7C2, D_R7C3, D_R7C4, D_R8C1, D_R8C2, D_R8C3, D_R8C4, D_R9C1, D_R9C2, D_R9C3, D_R9C4, D_R10C1, D_R10C2, D_R10C3, D_R10C4, D_R11C1, D_R11C2, D_R11C3, D_R11C4, D_R12C1, D_R12C2, D_R12C3, D_R12C4, D_R13C1, D_R13C2, D_R13C3, D_R13C4, D_R14C1, D_R14C2, D_R14C3, D_R14C4, D_R15C1, D_R15C2, D_R15C3, D_R15C4, D_R16C1, D_R16C2, D_R16C3, D_R16C4: LED; LED_1206_3216Metric_Pad1.42x1.75mm_Arrow_HandSolder
J1: CONN_ICSP_UART; PinHeader_1x08_P2.54mm_Vertical
JP1: JP_BYPASS_POLARITY_PROTECTION; SolderJumper-2_P1.3mm_Open_RoundedPad1.0x1.5mm
Q1: IRLML6402; SOT-23
R1, R2, R3, R4: 68; R_1206_3216Metric_Pad1.30x1.75mm_HandSolder
SW1, SW2, SW3: SW_Push; SW_SPST_Omron_B3FS-100xP
U1: PIC18F14 (SOP20/SSOP20); SO-20_12.8x7.5mm_P1.27mm
U2: 74HC154; SOIC-24W_7.5x15.4mm_P1.27mm

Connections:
/C1: D_R1C1.2 (A), D_R2C1.2 (A), D_R3C1.2 (A), D_R4C1.2 (A), D_R5C1.2 (A), D_R6C1.2 (A), D_R7C1.2 (A), D_R8C1.2 (A), D_R9C1.2 (A), D_R10C1.2 (A), D_R11C1.2 (A), D_R12C1.2 (A), D_R13C1.2 (A), D_R14C1.2 (A), D_R15C1.2 (A), D_R16C1.2 (A), R1.1
/C2: D_R1C2.2 (A), D_R2C2.2 (A), D_R3C2.2 (A), D_R4C2.2 (A), D_R5C2.2 (A), D_R6C2.2 (A), D_R7C2.2 (A), D_R8C2.2 (A), D_R9C2.2 (A), D_R10C2.2 (A), D_R11C2.2 (A), D_R12C2.2 (A), D_R13C2.2 (A), D_R14C2.2 (A), D_R15C2.2 (A), D_R16C2.2 (A), R2.1
/C3: D_R1C3.2 (A), D_R2C3.2 (A), D_R3C3.2 (A), D_R4C3.2 (A), D_R5C3.2 (A), D_R6C3.2 (A), D_R7C3.2 (A), D_R8C3.2 (A), D_R9C3.2 (A), D_R10C3.2 (A), D_R11C3.2 (A), D_R12C3.2 (A), D_R13C3.2 (A), D_R14C3.2 (A), D_R15C3.2 (A), D_R16C3.2 (A), R3.1
/C4: D_R1C4.2 (A), D_R2C4.2 (A), D_R3C4.2 (A), D_R4C4.2 (A), D_R5C4.2 (A), D_R6C4.2 (A), D_R7C4.2 (A), D_R8C4.2 (A), D_R9C4.2 (A), D_R10C4.2 (A), D_R11C4.2 (A), D_R12C4.2 (A), D_R13C4.2 (A), D_R14C4.2 (A), D_R15C4.2 (A), D_R16C4.2 (A), R4.1
/COL1: R1.2, U1.16 (RC0)
/COL2: R2.2, U1.15 (RC1)
/COL3: R3.2, U1.14 (RC2)
/COL4: R4.2, U1.7 (RC3)
/MCLR: J1.1, U1.4 (~MCLR/VPP/RA3)
/PGEC: J1.5, U1.18 (RA1/ICSPCLK)
/PGED: J1.4, U1.19 (RA0/ICSPDAT)
/R1: D_R1C1.1 (K), D_R1C2.1 (K), D_R1C3.1 (K), D_R1C4.1 (K), U2.1 (S0)
/R2: D_R2C1.1 (K), D_R2C2.1 (K), D_R2C3.1 (K), D_R2C4.1 (K), U2.2 (S1)
/R3: D_R3C1.1 (K), D_R3C2.1 (K), D_R3C3.1 (K), D_R3C4.1 (K), U2.3 (S2)
/R4: D_R4C1.1 (K), D_R4C2.1 (K), D_R4C3.1 (K), D_R4C4.1 (K), U2.4 (S3)
/R5: D_R5C1.1 (K), D_R5C2.1 (K), D_R5C3.1 (K), D_R5C4.1 (K), U2.5 (S4)
/R6: D_R6C1.1 (K), D_R6C2.1 (K), D_R6C3.1 (K), D_R6C4.1 (K), U2.6 (S5)
/R7: D_R7C1.1 (K), D_R7C2.1 (K), D_R7C3.1 (K), D_R7C4.1 (K), U2.7 (S6)
/R8: D_R8C1.1 (K), D_R8C2.1 (K), D_R8C3.1 (K), D_R8C4.1 (K), U2.8 (S7)
/R9: D_R9C1.1 (K), D_R9C2.1 (K), D_R9C3.1 (K), D_R9C4.1 (K), U2.9 (S8)
/R10: D_R10C1.1 (K), D_R10C2.1 (K), D_R10C3.1 (K), D_R10C4.1 (K), U2.10 (S9)
/R11: D_R11C1.1 (K), D_R11C2.1 (K), D_R11C3.1 (K), D_R11C4.1 (K), U2.11 (S10)
/R12: D_R12C1.1 (K), D_R12C2.1 (K), D_R12C3.1 (K), D_R12C4.1 (K), U2.13 (S11)
/R13: D_R13C1.1 (K), D_R13C2.1 (K), D_R13C3.1 (K), D_R13C4.1 (K), U2.14 (S12)
/R14: D_R14C1.1 (K), D_R14C2.1 (K), D_R14C3.1 (K), D_R14C4.1 (K), U2.15 (S13)
/R15: D_R15C1.1 (K), D_R15C2.1 (K), D_R15C3.1 (K), D_R15C4.1 (K), U2.16 (S14)
/R16: D_R16C1.1 (K), D_R16C2.1 (K), D_R16C3.1 (K), D_R16C4.1 (K), U2.17 (S15)
/ROW0: U1.6 (RC4), U2.23 (A0)
/ROW1: U1.5 (RC5), U2.22 (A1)
/ROW2: U1.8 (RC6), U2.21 (A2)
/ROW3: U1.9 (RC7), U2.20 (A3)
/SW1: SW1.1, U1.13 (RB4)
/SW2: SW2.1, U1.12 (RB5)
/SW3: SW3.1, U1.11 (RB6)
/TX: J1.7, U1.17 (RA2)
/VBATT: BT1.1 (+), JP1.1 (A), Q1.3 (D)
/~EN: U1.10 (RB7), U2.18 (E0)
GND: BT1.2 (-), C1.2, C2.2, C3.2, J1.3, Q1.1 (G), SW1.2, SW2.2, SW3.2, U1.20 (VSS), U2.12 (GND), U2.19 (E1)
VCC: C1.1, C2.1, C3.1, J1.2, JP1.2 (B), Q1.2 (S), U1.1 (VDD), U2.24 (VCC)
